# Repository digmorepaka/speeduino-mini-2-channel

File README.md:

# Features
* 75x78mm form factor
* 2 Injection channels (High-Z negative side switching)
* 2 Ignition channels (5V/12V)
* Up to 2 cylinder sequential, up to 4 cylinder paired mode
* Tacho output
* 1 Programable output
* Secondary serial
* Speeduino firmware

# Use cases
* Motorcycles
* ATVs
* Go karts
* Other small form factor installations

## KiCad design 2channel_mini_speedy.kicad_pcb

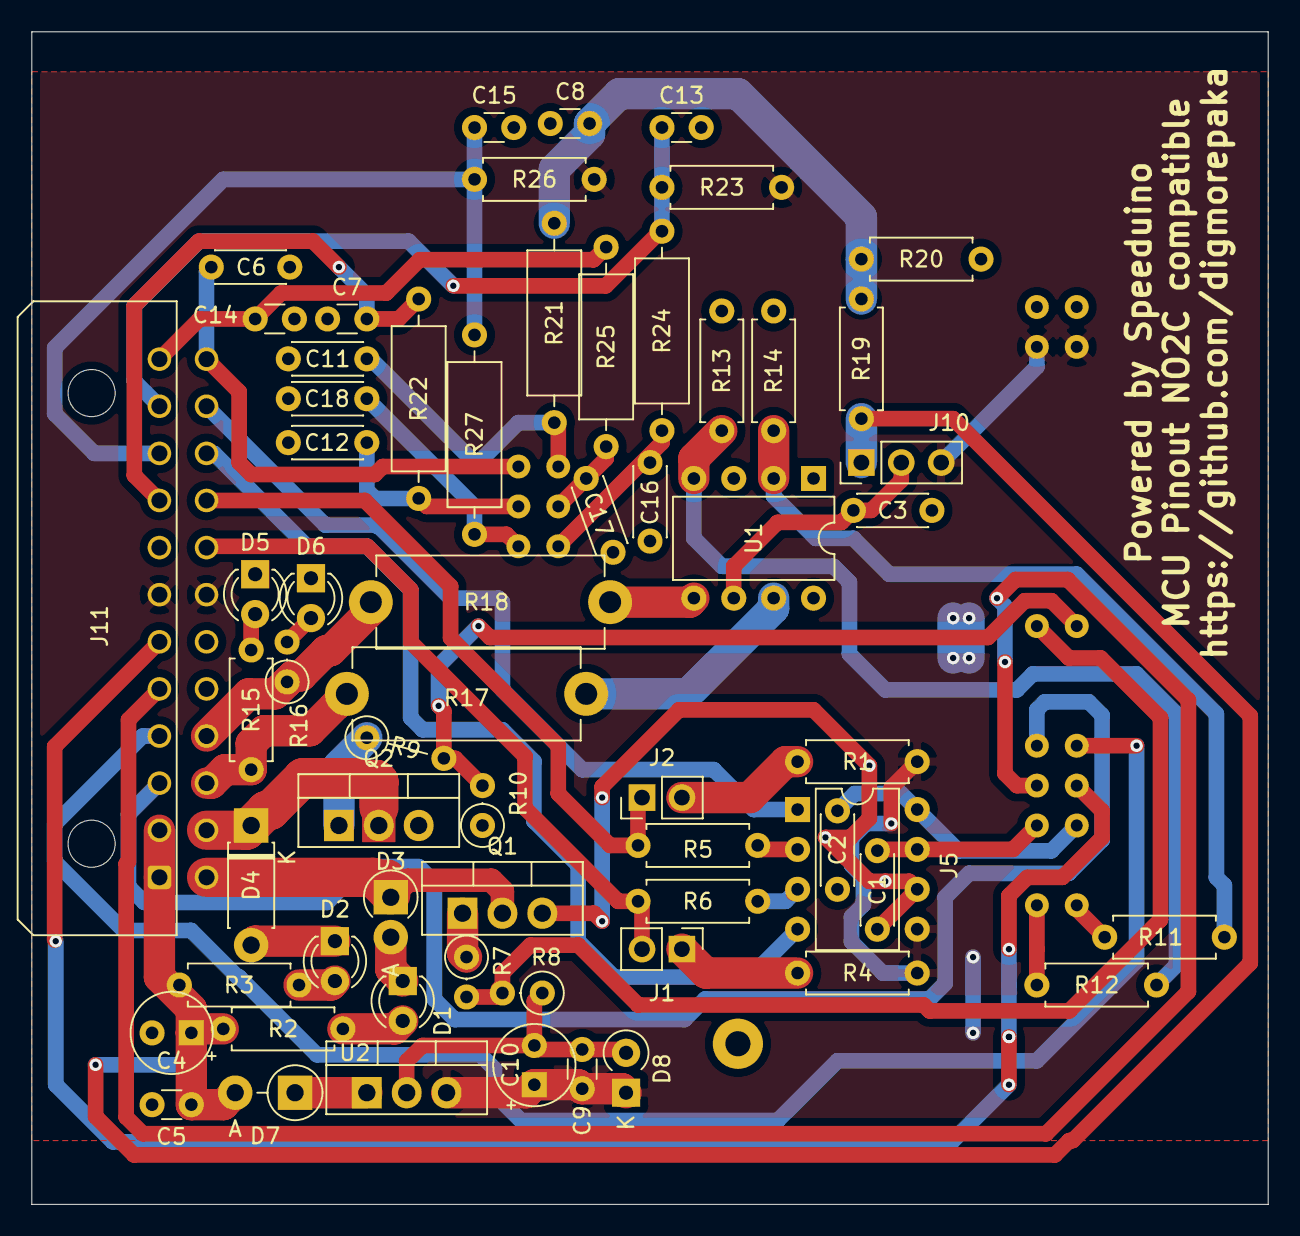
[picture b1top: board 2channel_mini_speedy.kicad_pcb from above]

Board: 2 copper layers, 78.7 x 74.7 mm, 63 parts (1 on the bottom side), 50 nets.

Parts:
C1, C11, C12, C16, C17, C18: 0.22uF; C_Disc_D4.3mm_W1.9mm_P5.00mm
C2: 0.01uF; C_Disc_D4.3mm_W1.9mm_P5.00mm
C3: 1uF; C_Disc_D4.3mm_W1.9mm_P5.00mm
C4: 10uF 35V; CP_Radial_Tantal_D5.0mm_P2.50mm
C5, C9: 0.1uF 50V; C_Disc_D3.0mm_W1.6mm_P2.50mm
C6: 0.3uF; C_Disc_D4.3mm_W1.9mm_P5.00mm
C7, C8, C13, C14, C15: 0.1uF; C_Disc_D3.0mm_W1.6mm_P2.50mm
C10: 47uF 10V; CP_Radial_Tantal_D5.0mm_P2.50mm
D1, D2, D5, D6: LED; LED_D3.0mm
D3: 1N4004; D_DO-41_SOD81_P2.54mm_Vertical_AnodeUp
D4: 1N4004; D_DO-41_SOD81_P7.62mm_Horizontal
D7: 1N5818; D_DO-41_SOD81_P3.81mm_Vertical_AnodeUp
D8: 1N5919BG; D_A-405_P2.54mm_Vertical_KathodeUp
J1: TACH 2 pullup; PinHeader_1x02_P2.54mm_Vertical
J2: TACH 1 pullup; PinHeader_1x02_P2.54mm_Vertical
J5: Signal conditioner; DIP-8_W7.62mm
J10: IGN Voltage sel; PinHeader_1x03_P2.54mm_Vertical
J11: Molex MicroFit 3.0 43045-2400/Amphenol ICC 101277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; Molex_Micro-Fit_3.0_43045-2400_2x12_P3.00mm_Horizontal
Q1, Q2: STP75N04-TO220; TO-220-3_Vertical
R1, R4, R5, R6, R11, R12, R20: 1K; R_Axial_DIN0207_L6.3mm_D2.5mm_P7.62mm_Horizontal
R2, R3: 680R; R_Axial_DIN0207_L6.3mm_D2.5mm_P7.62mm_Horizontal
R7: 1K; R_Axial_DIN0207_L6.3mm_D2.5mm_P2.54mm_Vertical
R8, R10: 100K; R_Axial_DIN0207_L6.3mm_D2.5mm_P2.54mm_Vertical
R9: 1K; R_Axial_DIN0207_L6.3mm_D2.5mm_P5.08mm_Vertical
R13, R14: 100K; R_Axial_DIN0207_L6.3mm_D2.5mm_P7.62mm_Horizontal
R15: 2.4K; R_Axial_DIN0207_L6.3mm_D2.5mm_P7.62mm_Horizontal
R16: 2.4K; R_Axial_DIN0207_L6.3mm_D2.5mm_P2.54mm_Vertical
R17, R18: 160R 2W; R_Axial_DIN0614_L14.3mm_D5.7mm_P15.24mm_Horizontal
R19: 3.9K; R_Axial_DIN0207_L6.3mm_D2.5mm_P7.62mm_Horizontal
R21, R22, R24, R25, R27: 470R; R_Axial_DIN0309_L9.0mm_D3.2mm_P12.70mm_Horizontal
R23, R26: 2.49K; R_Axial_DIN0207_L6.3mm_D2.5mm_P7.62mm_Horizontal
U1: TC4424EPA; DIP-8_W7.62mm
U2: LM2940T; TO-220-3_Vertical
U3: Mega2560-PRO; Mega2560-PRO-Stripped

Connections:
+5V: C9.1, C10.1, D8.1, J5.5, J10.3, J11.7, J11.19, R1.2, R4.2, R23.1, R26.1, U2.3, U3.5V
+12V: C4.1, C5.1, D7.2, J10.1, J11.1, J11.2, R2.2, R3.2, R19.1
BRV-SIG: C11.1, R21.1, U3.A1
CLT: C15.1, J11.10, R26.2, R27.2
CLT-SIG: C18.1, R27.1, U3.A4
D16: J11.5, U3.D16
GND: C1.1, C2.1, C3.2, C4.2, C5.2, C6.2, C7.2, C8.2, C9.2, C10.2, C11.2, C12.2, C13.2, C14.2, C15.2, C16.2, C17.2, C18.2, D5.1, D6.1, D8.2, J5.6, J11.8, J11.17, J11.18, Q1.3, Q2.3, R8.1, R10.1, R13.2, R14.1, R20.2, U1.3, U2.2, U3.GND
IAT: C13.1, J11.11, R23.2, R24.2
IAT-SIG: C16.1, R24.1, U3.A5
IGN1: J11.15, R15.1, R17.2
IGN1-SIG: R11.2, U3.D23
IGN2: J11.16, R16.1, R18.1
IGN2-SIG: R12.2, U3.D22
IGN_PWR: C3.1, J10.2, U1.6
INJ1: D3.1, J11.13, Q1.2
INJ1-SIG: R7.2, R8.2, U3.D8
INJ2: D4.1, J11.14, Q2.2
INJ2-SIG: R9.2, R10.2, U3.D9
MAP-SIG: C6.1, J11.24, U3.A0
unnamed: C8.1, R19.2, R20.1, R21.2
unnamed: D1.1, D3.2
unnamed: D1.2, R2.1
unnamed: D2.1, D4.2
unnamed: D2.2, R3.1
unnamed: D5.2, R15.2
unnamed: D6.2, R16.2
unnamed: D7.1, U2.1
unnamed: J1.1, R4.1
unnamed: J2.2, R1.1
unnamed: J5.2, R5.1
unnamed: J5.3, R6.1
unnamed: Q1.1, R7.1
unnamed: Q2.1, R9.1
unnamed: R11.1, R13.1, U1.2
unnamed: R12.1, R14.2, U1.4
unnamed: R17.1, U1.7
unnamed: R18.2, U1.5
O2: C7.1, J11.9, R22.2
O2-SIG: C12.1, R22.1, U3.A2
RX3: J11.4, U3.D15
TACH1: C2.2, J5.8, U3.D19
TACH2: C1.2, J5.7, U3.D18
TACHO-OUT: J11.6, U3.D17
TPS: C14.1, J11.12, R25.2
TPS-SIG: C17.1, R25.1, U3.A3
TX3: J11.3, U3.D14
VR1+: J2.1, J11.21, R5.2
VR1-: J5.1, J11.23
VR2+: J1.2, J11.20, R6.2
VR2-: J5.4, J11.22

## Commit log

2021-11-02 fixed mosfet pinouts and ground plane
